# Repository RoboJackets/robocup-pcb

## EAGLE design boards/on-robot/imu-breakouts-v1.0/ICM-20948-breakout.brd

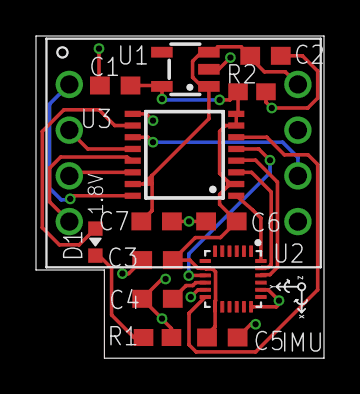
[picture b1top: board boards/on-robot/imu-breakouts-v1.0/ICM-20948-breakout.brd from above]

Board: 2 copper layers, 16.0 x 17.9 mm, 15 parts (1 on the bottom side), 16 nets.

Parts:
C1, C2: 1uF; C0603
C3, C4, C6, C7: 0.1uF; C0603
C5: 1.0uF; C0603
D1: GREEN; CHIP-LED0603
KIT1: IMU
R1: 220; R0603W
R2: 50k; R0603W
U1: NCP161; SOT-23-5
U2: ICM-20948
U3: TXB0106; TSSOP-16
U$1: ROBOBUZZ_0.4X

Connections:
!CS!/1.8V: U2.22, U3.4
!CS!/3.3V: KIT1.4, U3.13
+1.8V: C1.1, C3.1, C5.1, C6.1, R2.1, U1.5, U2.8, U2.13, U3.2, U3.7, U3.8
+1.8V-D1-OUT: D1.C, R1.2
+3.3V: C2.1, C7.1, KIT1.8, U1.1, U1.3, U3.15
CLK/1.8V: U2.23, U3.3
CLK/3.3V: KIT1.3, U3.14
GND: C1.2, C2.2, C3.2, C4.2, C5.2, C6.2, C7.2, KIT1.5, R1.1, R2.2, U1.2, U2.11, U2.18, U2.20, U3.9
INT/1.8V: U2.12, U3.6
INT/3.3V: KIT1.6, U3.11
MISO/1.8V: U2.9, U3.5
MISO/3.3V: KIT1.2, U3.12
MOSI/1.8V: U2.24, U3.1
MOSI/3.3V: KIT1.1, U3.16
PRE-LED-3.3V: D1.A, U3.10
REGOUT: C4.1, U2.10

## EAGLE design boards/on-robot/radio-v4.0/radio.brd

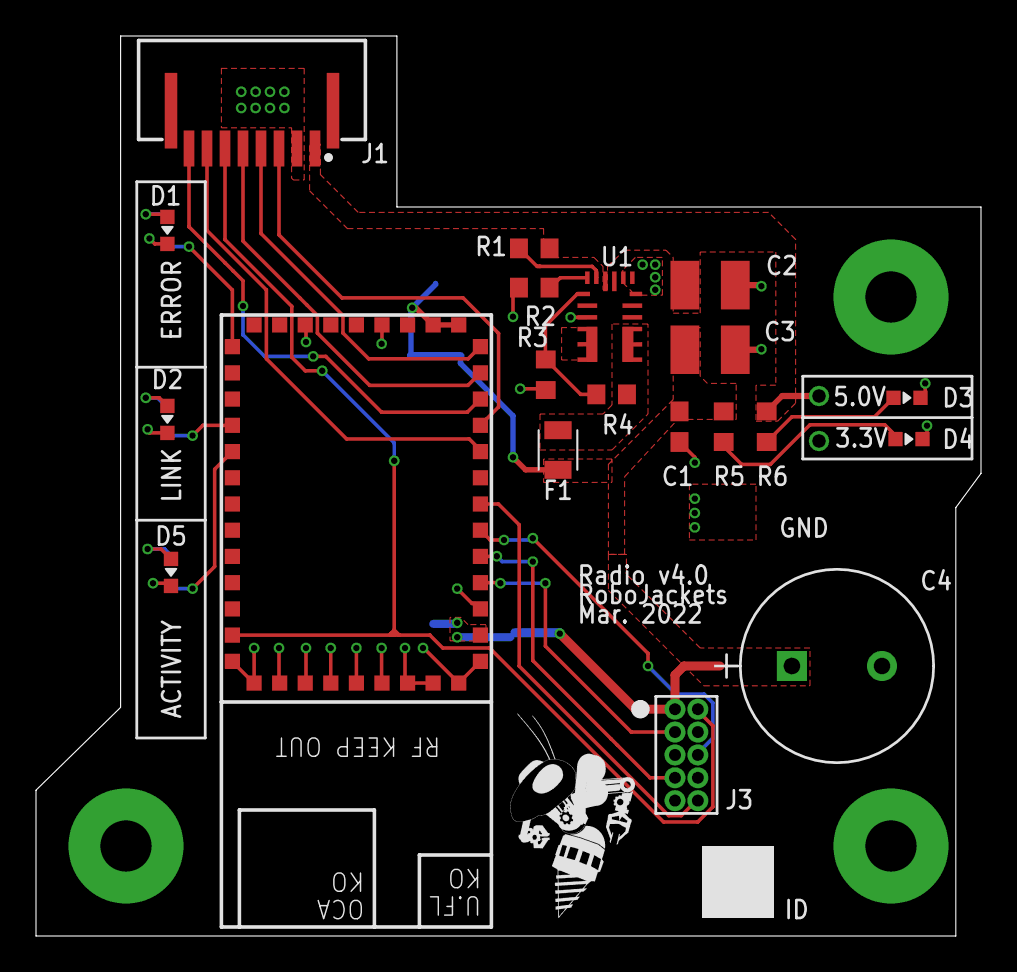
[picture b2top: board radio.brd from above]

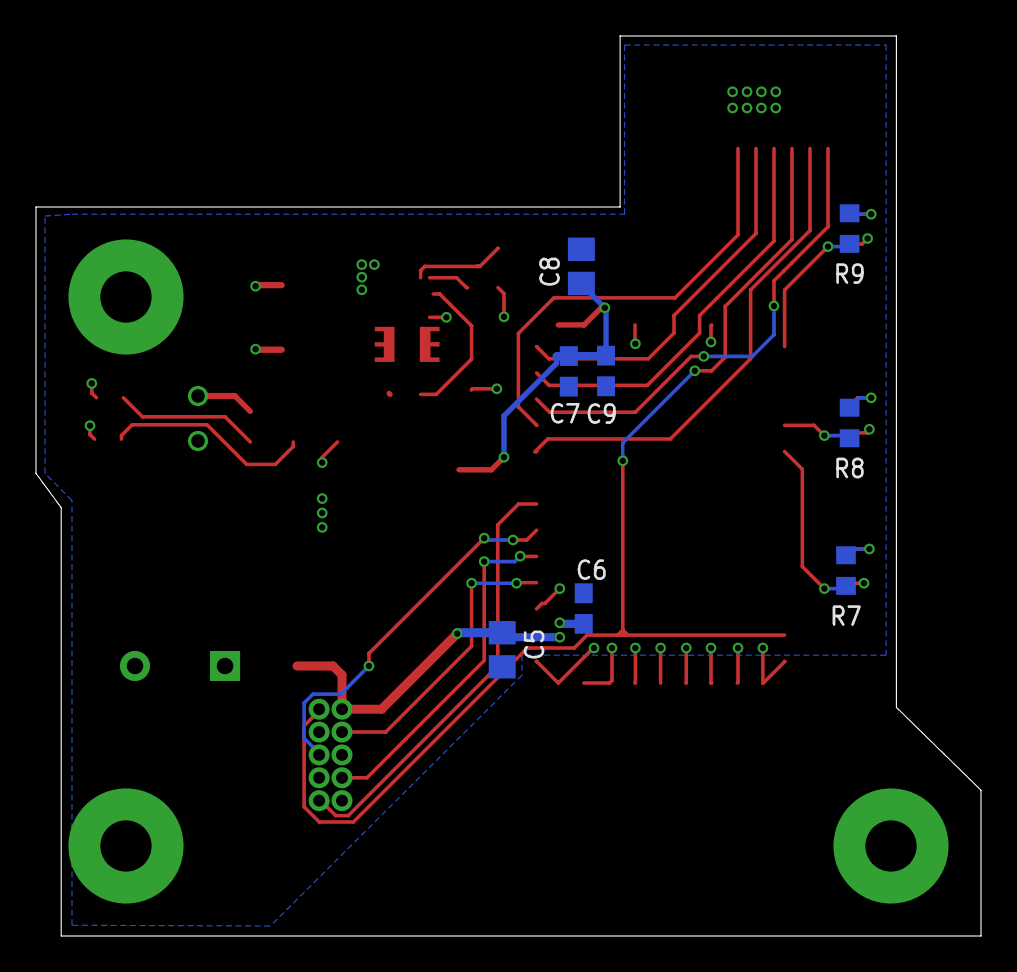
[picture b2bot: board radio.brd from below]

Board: 2 copper layers, 52.5 x 50.0 mm, 29 parts (8 on the bottom side), 25 nets.

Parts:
$$U1: ISM43340
C1, C6, C7: 0.1uF; C0603
C2: 10uF 16V; C1210
C3: 22uF; C1210
C4: 220uF; CAP_PAN_10X12.5
C5, C8: 10uF; C0805
C9: 1uF; C0603
D1: RED; CHIP-LED0603
D2, D3, D4: GREEN; CHIP-LED0603
D5: YELLOW; CHIP-LED0603
F1: 0805L200SLTHYR; FUSC2113X75
J1: SFW8; SFW8R-1ST
J2: FTSH-105-01-F-D-K; CONN_FTSH-105-01-F-D-K_SAI
R1: 100k; R0603
R2: 88.7k 1%; R0603
R3: 45.3k 1%; R0603
R4: 143.0k 1%; R0603
R5: 680; R0603
R6: 1k; R0603
R7, R8, R9: 200; R0603
U1: MPM3620GQV-P
U$2: ROBOBUZZ_0.6X

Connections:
3V3_PWR_IND: D4.A, R5.1
5V_PWR_IND: D3.A, R6.1
!CS!_RAD: $$U1.P$12, J1.5
!RST!_GLB: $$U1.P$34, J1.6, J2.2
+3.3V: $$U1.P$2, $$U1.P$14, $$U1.P$15, C1.1, C3.1, C4.1, C5.1, C6.1, C7.1, C8.1, C9.1, F1.2, J2.1, R5.2
+5.0V: C2.1, J1.1, R1.1, R6.2, U1.16
AAM: R2.2, U1.18
DBG_ACT_RAD: $$U1.P$27, R7.1
DBG_ERR: D1.A, R9.2
DBG_ERR_RAD: $$U1.P$23, R9.1
DBG_LNK_RAD: $$U1.P$26, R8.1
DGB_ACT: D5.A, R7.2
DGB_LNK: D2.A, R8.2
EN: R1.2, U1.17
FB: R3.2, R4.1, U1.1
GND: $$U1.P$1, $$U1.P$3, $$U1.P$17, $$U1.P$20, $$U1.P$35, $$U1.P$36, $$U1.P$37, $$U1.P$38, $$U1.P$39, $$U1.P$40, $$U1.P$41, $$U1.P$42, $$U1.P$43, $$U1.P$44, C1.2, C2.2, C3.2, C4.2, C5.2, C6.2, C7.2, C8.2, C9.2, D1.C, D2.C, D3.C, D4.C, D5.C, J1.2, J2.4, J2.5, J2.9, R2.1, R3.1, U1.3, U1.12, U1.13, U1.14
INT_RAD: $$U1.P$13, J1.4
MISO: $$U1.P$10, J1.3
MOSI: $$U1.P$9, J1.7
PRE-FUSE: F1.1, R4.2, U1.789
SCK: $$U1.P$11, J1.8
TCK_RAD: $$U1.P$5, J2.7
TDI_RAD: $$U1.P$6, J2.6
TDO_RAD: $$U1.P$7, J2.10
TMS_RAD: $$U1.P$4, J2.3

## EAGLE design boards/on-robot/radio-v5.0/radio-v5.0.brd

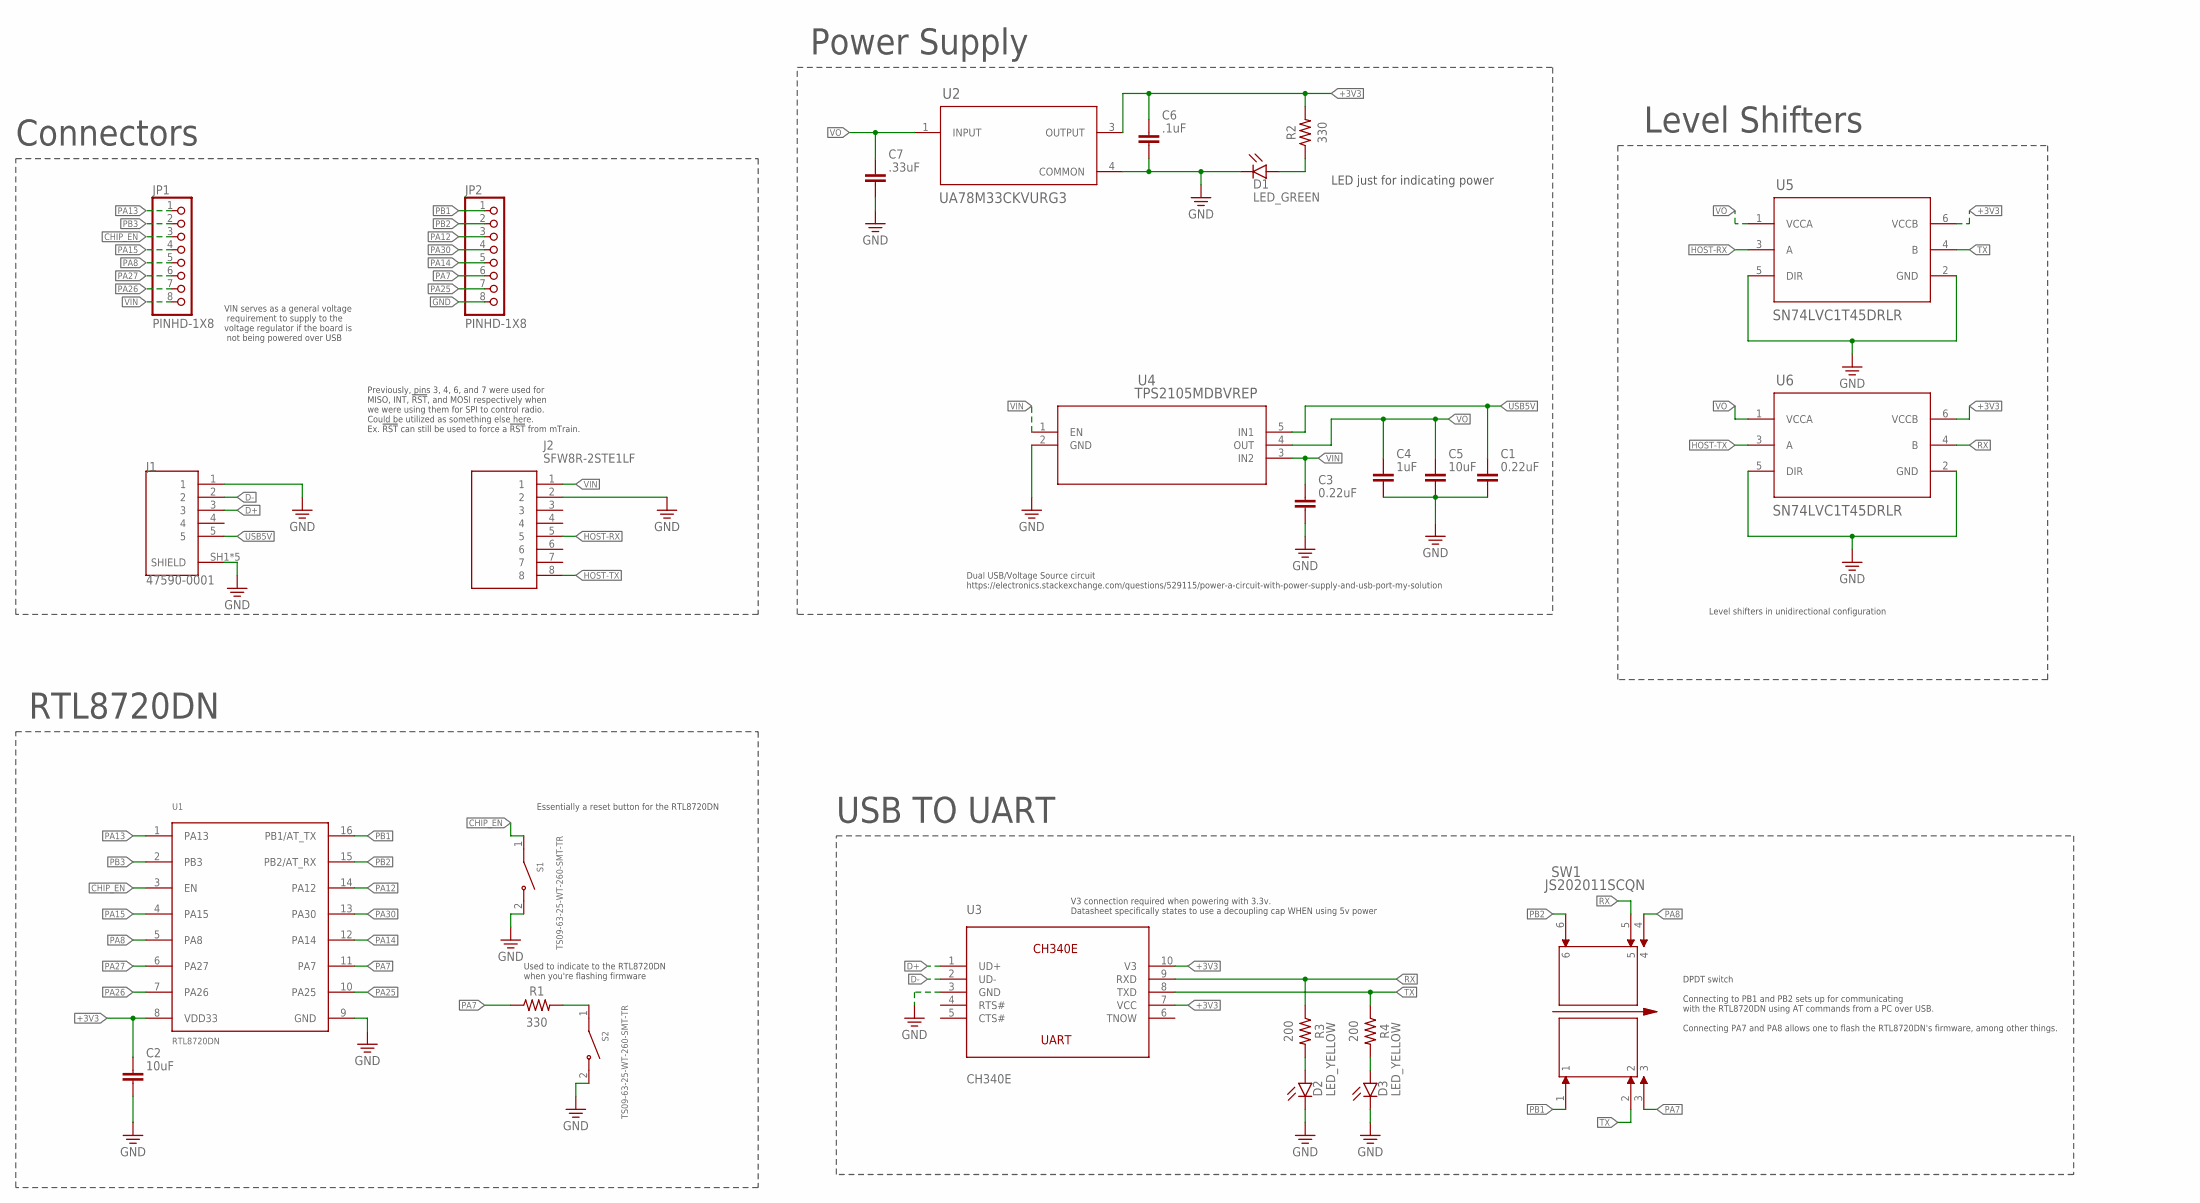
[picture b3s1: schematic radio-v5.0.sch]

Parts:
C1, C3: 0.22uF; CAPC1608X85
C2, C5: 10uF; CAPC1608X85
C4: 1uF; CAPC1608X85
C6: .1uF; CAPC1608X85
C7: .33uF; CAPC1608X85
D1: LED_GREEN; LEDC1608X55N_FLAT-B
D2, D3: LED_YELLOW; LEDC1608X55N_FLAT-B
J1: 47590-0001; MOLEX_47590-0001
J2: SFW8R-2STE1LF; SFW8R2STE1LF
JP1, JP2: PINHD-1X8; 1X08
R1, R2: 330; RESC1608X60
R3, R4: 200; RESC1608X60
S1, S2: TS09-63-25-WT-260-SMT-TR; SW_TS09-63-25-WT-260-SMT-TR
SW1: JS202011SCQN; SW_JS202011SCQN
U1: RTL8720DN
U2: UA78M33CKVURG3; KVU0003A_N
U3: CH340E; MS0P10
U4: TPS2105MDBVREP; DBV5_TEX
U5, U6: SN74LVC1T45DRLR; DRL0006A

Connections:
+3V3: C2.1, C6.1, R2.2, U1.8 (VDD33), U2.3 (OUTPUT), U3.7 (VCC), U3.10 (V3), U5.6 (VCCB), U6.6 (VCCB)
CHIP_EN: JP1.3, S1.1, U1.3 (EN)
D+: J1.3, U3.1 (UD+)
D-: J1.2, U3.2 (UD-)
GND: C1.2, C2.2, C3.2, C4.2, C5.2, C6.2, C7.2, D1.C, D2.C, D3.C, J1.SH1 (SHIELD), J1.SH2 (SHIELD), J1.SH3 (SHIELD), J1.SH4 (SHIELD), J1.SH5 (SHIELD), J2.2, JP2.8, S1.2, S2.2, U1.9 (GND), U2.4 (COMMON), U3.3 (GND), U4.2 (GND), U5.2 (GND), U5.5 (DIR), U6.2 (GND), U6.5 (DIR)
HOST-RX: J2.5, U5.3 (A)
HOST-TX: J2.8, U6.3 (A)
unnamed: R1.2, S2.1
unnamed: D2.A, R3.2
unnamed: D1.A, R2.1
unnamed: D3.A, R4.2
PA7: JP2.6, R1.1, SW1.3, U1.11 (PA7)
PA8: JP1.5, SW1.4, U1.5 (PA8)
PA12: JP2.3, U1.14 (PA12)
PA13: JP1.1, U1.1 (PA13)
PA14: JP2.5, U1.12 (PA14)
PA15: JP1.4, U1.4 (PA15)
PA25: JP2.7, U1.10 (PA25)
PA26: JP1.7, U1.7 (PA26)
PA27: JP1.6, U1.6 (PA27)
PA30: JP2.4, U1.13 (PA30)
PB1: JP2.1, SW1.1, U1.16 (PB1/AT_TX)
PB2: JP2.2, SW1.6, U1.15 (PB2/AT_RX)
PB3: JP1.2, U1.2 (PB3)
RX: R3.1, SW1.5, U3.9 (RXD), U6.4 (B)
TX: R4.1, SW1.2, U3.8 (TXD), U5.4 (B)
USB5V: C1.1, J1.5, U4.5 (IN1)
VIN: C3.1, J2.1, JP1.8, U4.1 (EN), U4.3 (IN2)
VO: C4.1, C5.1, C7.1, U2.1 (INPUT), U4.4 (OUT), U5.1 (VCCA), U6.1 (VCCA)

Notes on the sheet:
Connectors
VIN serves as a general voltage requirement to supply to the voltage regulator if the board is not being powered over USB
Power Supply
RTL8720DN
Dual USB/Voltage Source circuit https://electronics.stackexchange.com/questions/529115/power-a-circuit-with-power-supply-and-usb-port-my-solution
USB TO UART
DPDT switch Connecting to PB1 and PB2 sets up for communicating with the RTL8720DN using AT commands from a PC over USB. Connecting PA7 and PA8 allows one to flash the RTL8720DN's firmware, among other things.
V3 connection required when powering with 3.3v. Datasheet specifically states to use a decoupling cap WHEN using 5v power
Essentially a reset button for the RTL8720DN
Used to indicate to the RTL8720DN when you're flashing firmware
LED just for indicating power
Previously, pins 3, 4, 6, and 7 were used for MISO, INT, !RST!, and MOSI respectively when we were using them for SPI to control radio. Could be utilized as something else here. Ex. !RST! can still be used to force a !RST! from mTrain.
Level Shifters
Level shifters in unidirectional configuration

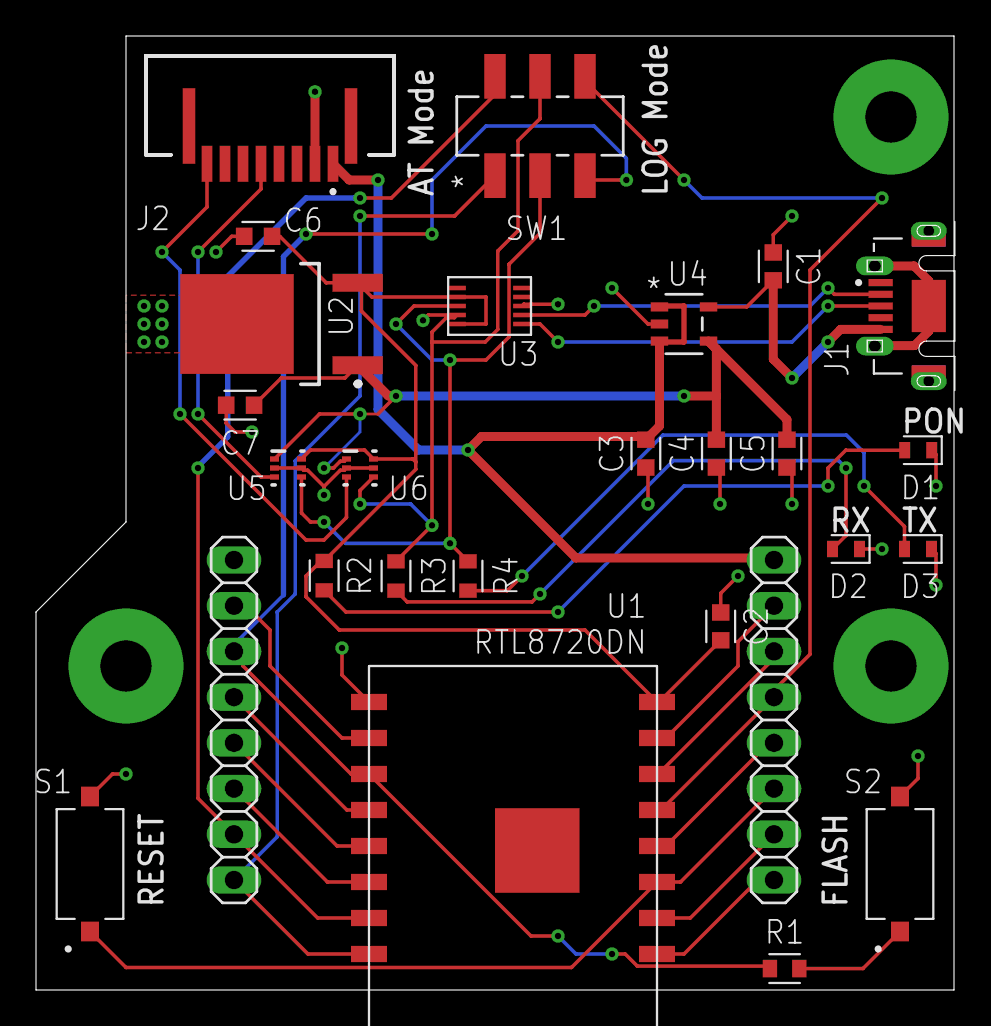
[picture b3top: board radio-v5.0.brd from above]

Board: 2 copper layers, 51.0 x 53.0 mm, 28 parts (1 on the bottom side), 29 nets.

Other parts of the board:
U$1: ROBOBUZZ_1.0X

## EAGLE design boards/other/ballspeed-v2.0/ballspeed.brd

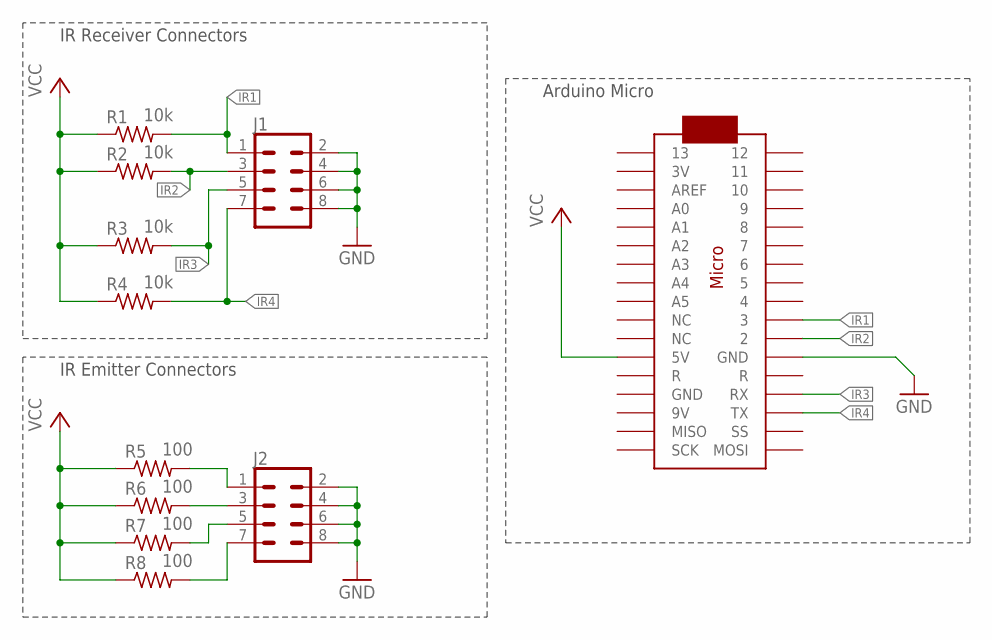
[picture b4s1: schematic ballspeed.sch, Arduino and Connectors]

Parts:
J1, J2: CONN_04X2; 2X4
R1, R2, R3, R4: 10k; R0603W
R5, R6, R7, R8: 100; R0603W
U$1: ARDUINOMICRO

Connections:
GND: J1.2, J1.4, J1.6, J1.8, J2.2, J2.4, J2.6, J2.8, U$1.P$21 (GND)
IR1: J1.1, R1.2 (PIN2), U$1.P$10 (3)
IR1-3.3V: J2.1, R5.2 (PIN2)
IR2: J1.3, R2.2 (PIN2), U$1.P$11 (2)
IR2-3.3V: J2.3, R6.2 (PIN2)
IR3: J1.5, R3.2 (PIN2), U$1.P$14 (RX)
IR3-3.3V: J2.5, R7.2 (PIN2)
IR4: J1.7, R4.2 (PIN2), U$1.P$15 (TX)
IR4-3.3V: J2.7, R8.2 (PIN2)
VCC: R1.1 (PIN1), R2.1 (PIN1), R3.1 (PIN1), R4.1 (PIN1), R5.1 (PIN1), R6.1 (PIN1), R7.1 (PIN1), R8.1 (PIN1), U$1.P$23 (5V)

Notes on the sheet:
IR Emitter Connectors
IR Receiver Connectors
Arduino Micro

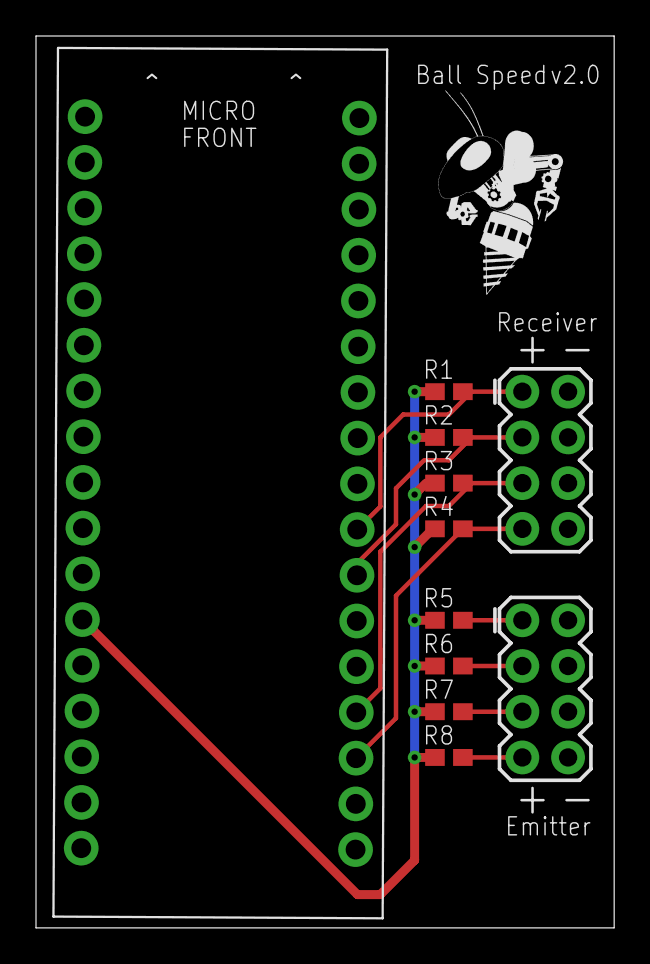
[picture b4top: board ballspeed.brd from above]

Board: 2 copper layers, 32.1 x 49.6 mm, 12 parts (0 on the bottom side), 10 nets.

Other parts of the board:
U$3: ROBOBUZZ_0.6X

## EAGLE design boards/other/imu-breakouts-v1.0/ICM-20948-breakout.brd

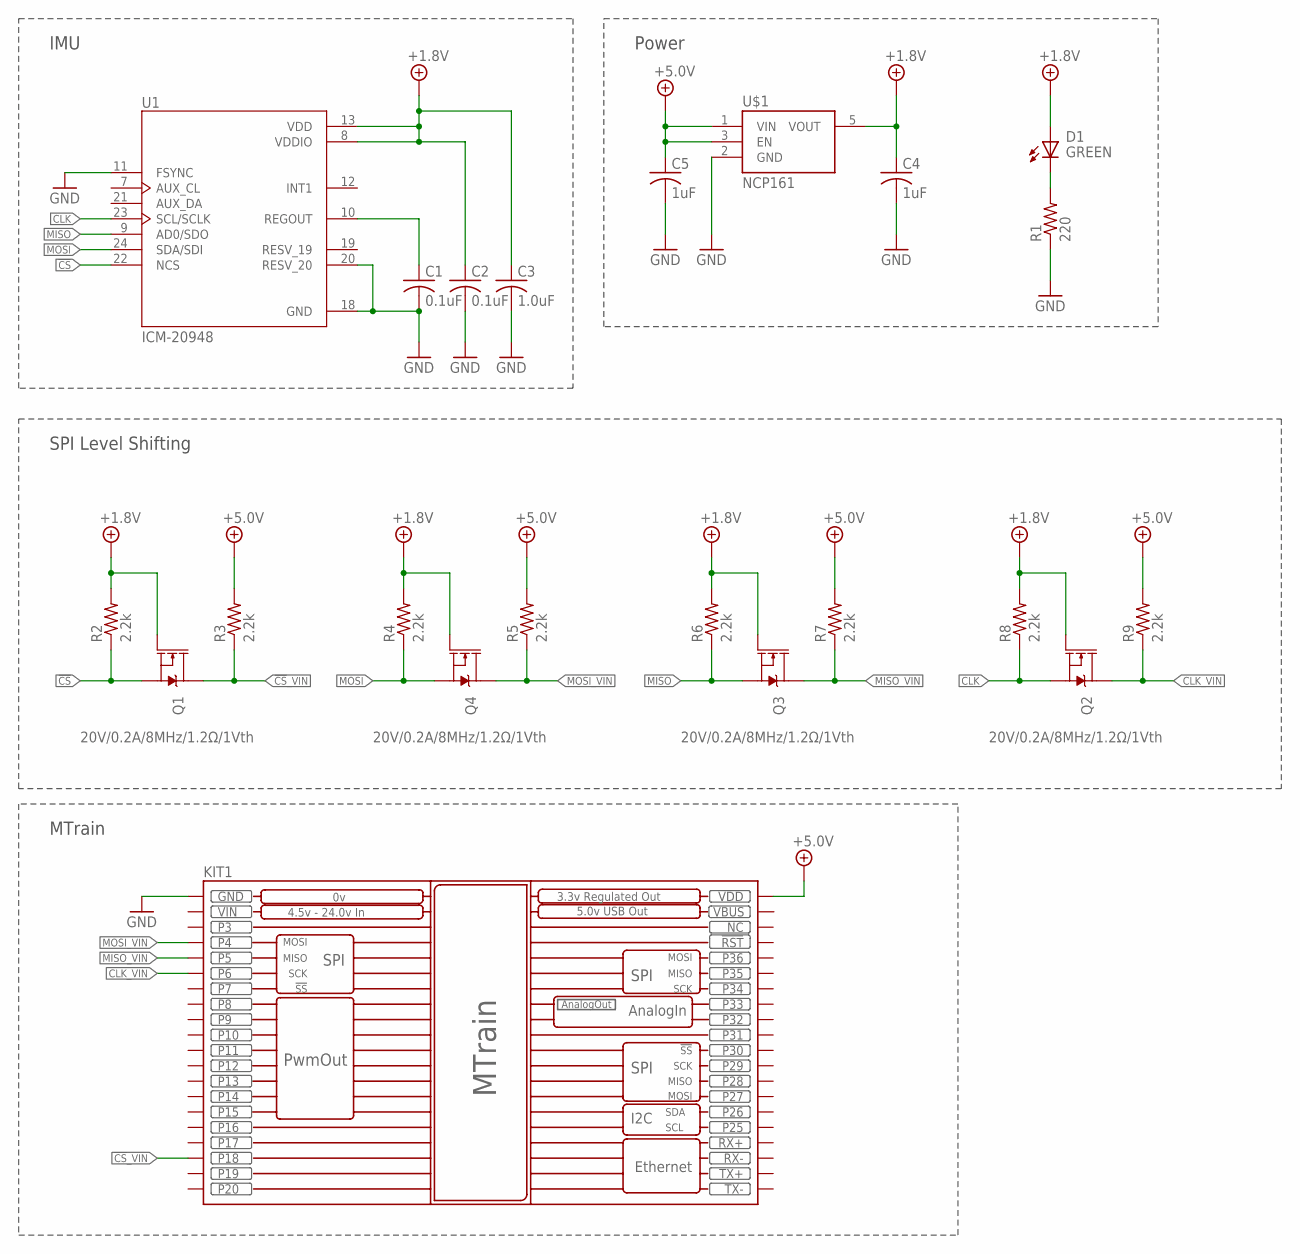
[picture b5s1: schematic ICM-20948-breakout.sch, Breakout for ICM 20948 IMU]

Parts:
C1, C2: 0.1uF; C0603
C3: 1.0uF; C0603
C4, C5: 1uF; C0603
D1: GREEN; CHIP-LED0603
KIT1: MTRAIN; MTRAIN-KIT
Q1, Q2, Q3, Q4: 20V/0.2A/8MHz/1.2Ω/1Vth; SOT-416FL
R1: 220; R0603W
R2, R3, R4, R5, R6, R7, R8, R9: 2.2k; R0603W
U1: ICM-20948
U$1: NCP161; SOT-23-5

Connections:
!CS!: Q1.2 (S), R2.1 (PIN1), U1.22 (NCS)
!CS!_VIN: KIT1.P$18 (P18), Q1.3 (D), R3.1 (PIN1)
+1.8V: C2.1, C3.1, C4.1, D1.A, Q1.1 (G), Q2.1 (G), Q3.1 (G), Q4.1 (G), R2.2 (PIN2), R4.2 (PIN2), R6.2 (PIN2), R8.2 (PIN2), U1.8 (VDDIO), U1.13 (VDD), U$1.5 (VOUT)
+3.3V: C5.1, R3.2 (PIN2), R5.2 (PIN2), R7.2 (PIN2), R9.2 (PIN2), U$1.1 (VIN), U$1.3 (EN)
+5.0V: KIT1.VDD
CLK: Q2.2 (S), R8.1 (PIN1), U1.23 (SCL/SCLK)
CLK_VIN: KIT1.P$6 (P6), Q2.3 (D), R9.1 (PIN1)
GND: C1.2, C2.2, C3.2, C4.2, C5.2, KIT1.GND, R1.1 (PIN1), U1.11 (FSYNC), U1.18 (GND), U1.20 (RESV_20), U$1.2 (GND)
MISO: Q3.2 (S), R6.1 (PIN1), U1.9 (AD0/SDO)
MISO_VIN: KIT1.P$5 (P5), Q3.3 (D), R7.1 (PIN1)
MOSI: Q4.2 (S), R4.1 (PIN1), U1.24 (SDA/SDI)
MOSI_VIN: KIT1.P$4 (P4), Q4.3 (D), R5.1 (PIN1)
unnamed: D1.C (K), R1.2 (PIN2)
REGOUT: C1.1, U1.10 (REGOUT)
VBUS: KIT1.VBUS
VIN: KIT1.VIN

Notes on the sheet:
IMU
MTrain
Power
SPI Level Shifting

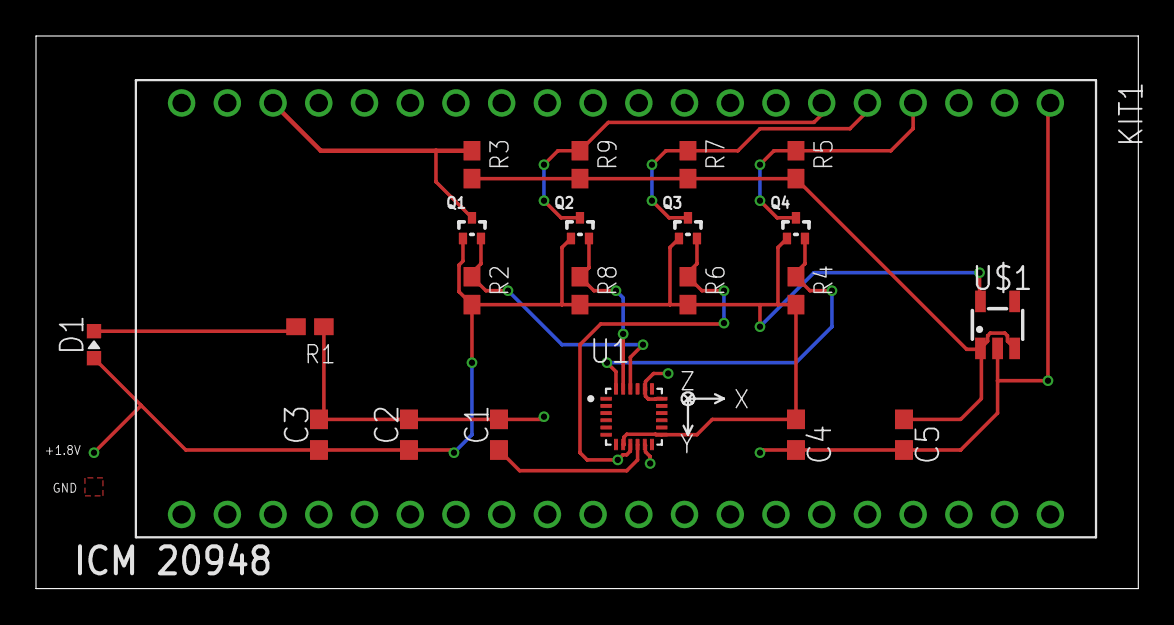
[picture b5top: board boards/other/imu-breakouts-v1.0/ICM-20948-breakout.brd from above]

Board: 2 copper layers, 61.2 x 30.7 mm, 22 parts (0 on the bottom side), 13 nets.

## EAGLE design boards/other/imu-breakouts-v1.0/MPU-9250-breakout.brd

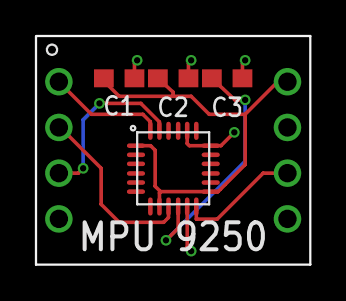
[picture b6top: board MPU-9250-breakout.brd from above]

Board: 2 copper layers, 15.2 x 12.7 mm, 5 parts (0 on the bottom side), 7 nets.

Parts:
C1: 0.01uF; C0603
C2, C3: 0.1uF; C0603
IC1: MPU-9250; QFN-24-4MM2
KIT1: IMUIMU-KIT; IMU-KIT

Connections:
+3.3V: C1.1, C2.1, IC1.1, IC1.8, IC1.13, KIT1.8
CLK: IC1.23, KIT1.3
GND: C1.2, C2.2, C3.2, IC1.11, IC1.18, IC1.20, KIT1.5
INT: IC1.12, KIT1.6
MISO: IC1.9, KIT1.2
MOSI: IC1.24, KIT1.1
unnamed: C3.1, IC1.10

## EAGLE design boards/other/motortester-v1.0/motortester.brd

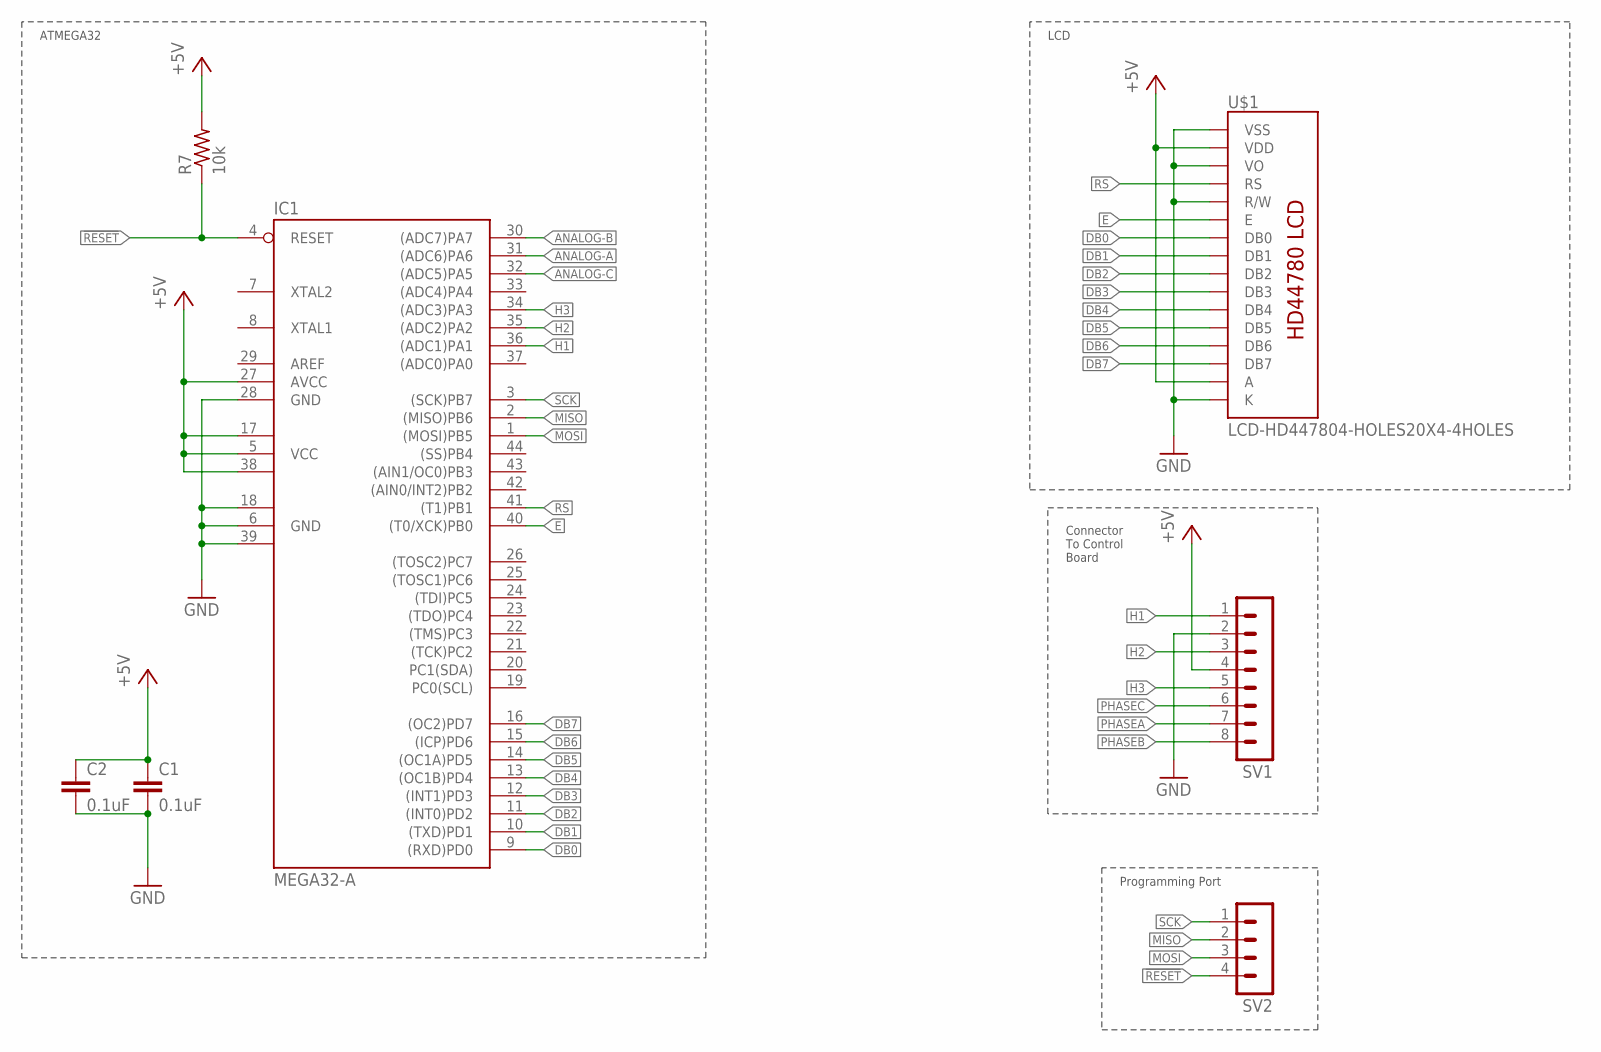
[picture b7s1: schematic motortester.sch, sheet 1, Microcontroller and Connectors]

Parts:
C1, C2: 0.1uF; C0603
IC1: MEGA32-A; TQFP44
R7: 10k; R0603
SV1: MA08-1
SV2: MA04-1
U$1: LCD-HD447804-HOLES20X4-4HOLES; LCD-20X4-4HOLES

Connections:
!RESET!: IC1.4 (RESET), R7.1, SV2.4
ANALOG-A: IC1.31 ((ADC6)PA6); also elsewhere on the board
ANALOG-B: IC1.30 ((ADC7)PA7); also elsewhere on the board
ANALOG-C: IC1.32 ((ADC5)PA5); also elsewhere on the board
DB0: IC1.9 ((RXD)PD0), U$1.P$7 (DB0)
DB1: IC1.10 ((TXD)PD1), U$1.P$8 (DB1)
DB2: IC1.11 ((INT0)PD2), U$1.P$9 (DB2)
DB3: IC1.12 ((INT1)PD3), U$1.P$10 (DB3)
DB4: IC1.13 ((OC1B)PD4), U$1.P$11 (DB4)
DB5: IC1.14 ((OC1A)PD5), U$1.P$12 (DB5)
DB6: IC1.15 ((ICP)PD6), U$1.P$13 (DB6)
DB7: IC1.16 ((OC2)PD7), U$1.P$14 (DB7)
E: IC1.40 ((T0/XCK)PB0), U$1.P$6 (E)
GND: C1.2, C2.2, IC1.6 (GND), IC1.18 (GND1), IC1.28 (GND), IC1.39 (GND2), SV1.2, U$1.P$1 (VSS), U$1.P$3 (VO), U$1.P$5 (R/W), U$1.P$16 (K)
H1: IC1.36 ((ADC1)PA1), SV1.1
H2: IC1.35 ((ADC2)PA2), SV1.3
H3: IC1.34 ((ADC3)PA3), SV1.5
MISO: IC1.2 ((MISO)PB6), SV2.2
MOSI: IC1.1 ((MOSI)PB5), SV2.3
PHASEA: SV1.7; also elsewhere on the board
PHASEB: SV1.8; also elsewhere on the board
PHASEC: SV1.6; also elsewhere on the board
RS: IC1.41 ((T1)PB1), U$1.P$4 (RS)
SCK: IC1.3 ((SCK)PB7), SV2.1
VCC: C1.1, C2.1, IC1.5 (VCC), IC1.17 (VCC1), IC1.27 (AVCC), IC1.38 (VCC2), R7.2, SV1.4, U$1.P$2 (VDD), U$1.P$15 (A)

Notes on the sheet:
ATMEGA32
LCD
Connector To Control Board
Programming Port

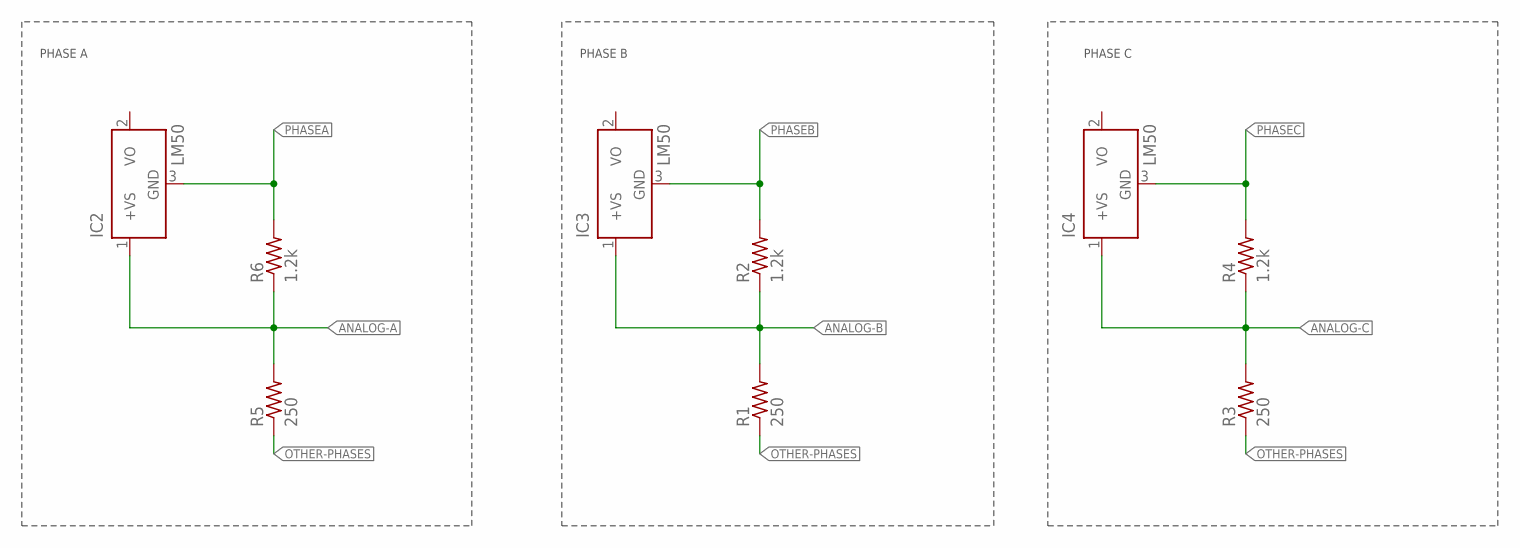
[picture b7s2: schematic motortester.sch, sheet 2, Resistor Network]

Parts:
IC2, IC3, IC4: LM50; SOT23
R1, R3, R5: 250; R0603
R2, R4, R6: 1.2k; R0603

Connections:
ANALOG-A: IC2.1 (+VS), R5.2, R6.1; also elsewhere on the board
ANALOG-B: IC3.1 (+VS), R1.2, R2.1; also elsewhere on the board
ANALOG-C: IC4.1 (+VS), R3.2, R4.1; also elsewhere on the board
OTHER-PHASES: R1.1, R3.1, R5.1
PHASEA: IC2.3 (GND), R6.2; also elsewhere on the board
PHASEB: IC3.3 (GND), R2.2; also elsewhere on the board
PHASEC: IC4.3 (GND), R4.2; also elsewhere on the board

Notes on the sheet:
PHASE A
PHASE B
PHASE C

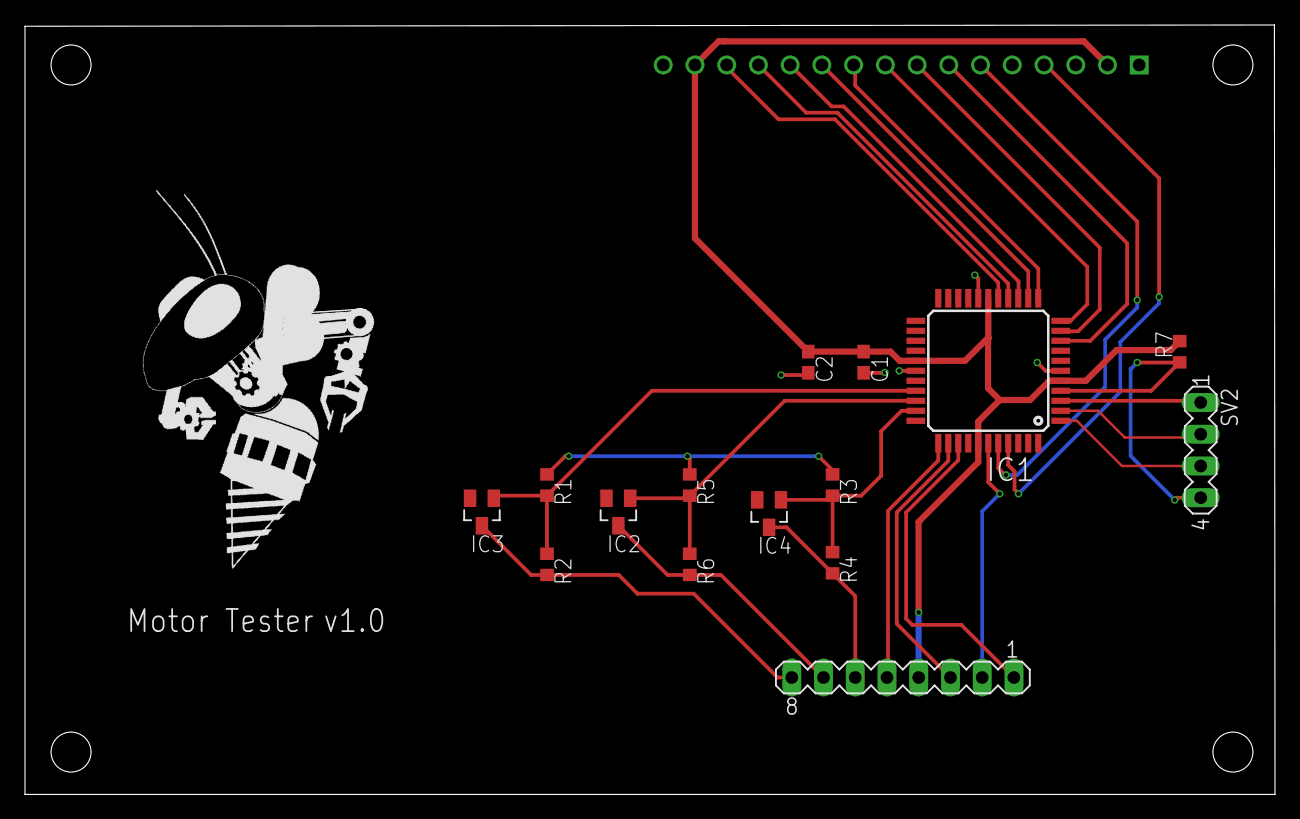
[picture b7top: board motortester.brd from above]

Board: 2 copper layers, 100.1 x 61.6 mm, 17 parts (1 on the bottom side), 26 nets.

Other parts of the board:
U$2: ROBOBUZZ_1.4X

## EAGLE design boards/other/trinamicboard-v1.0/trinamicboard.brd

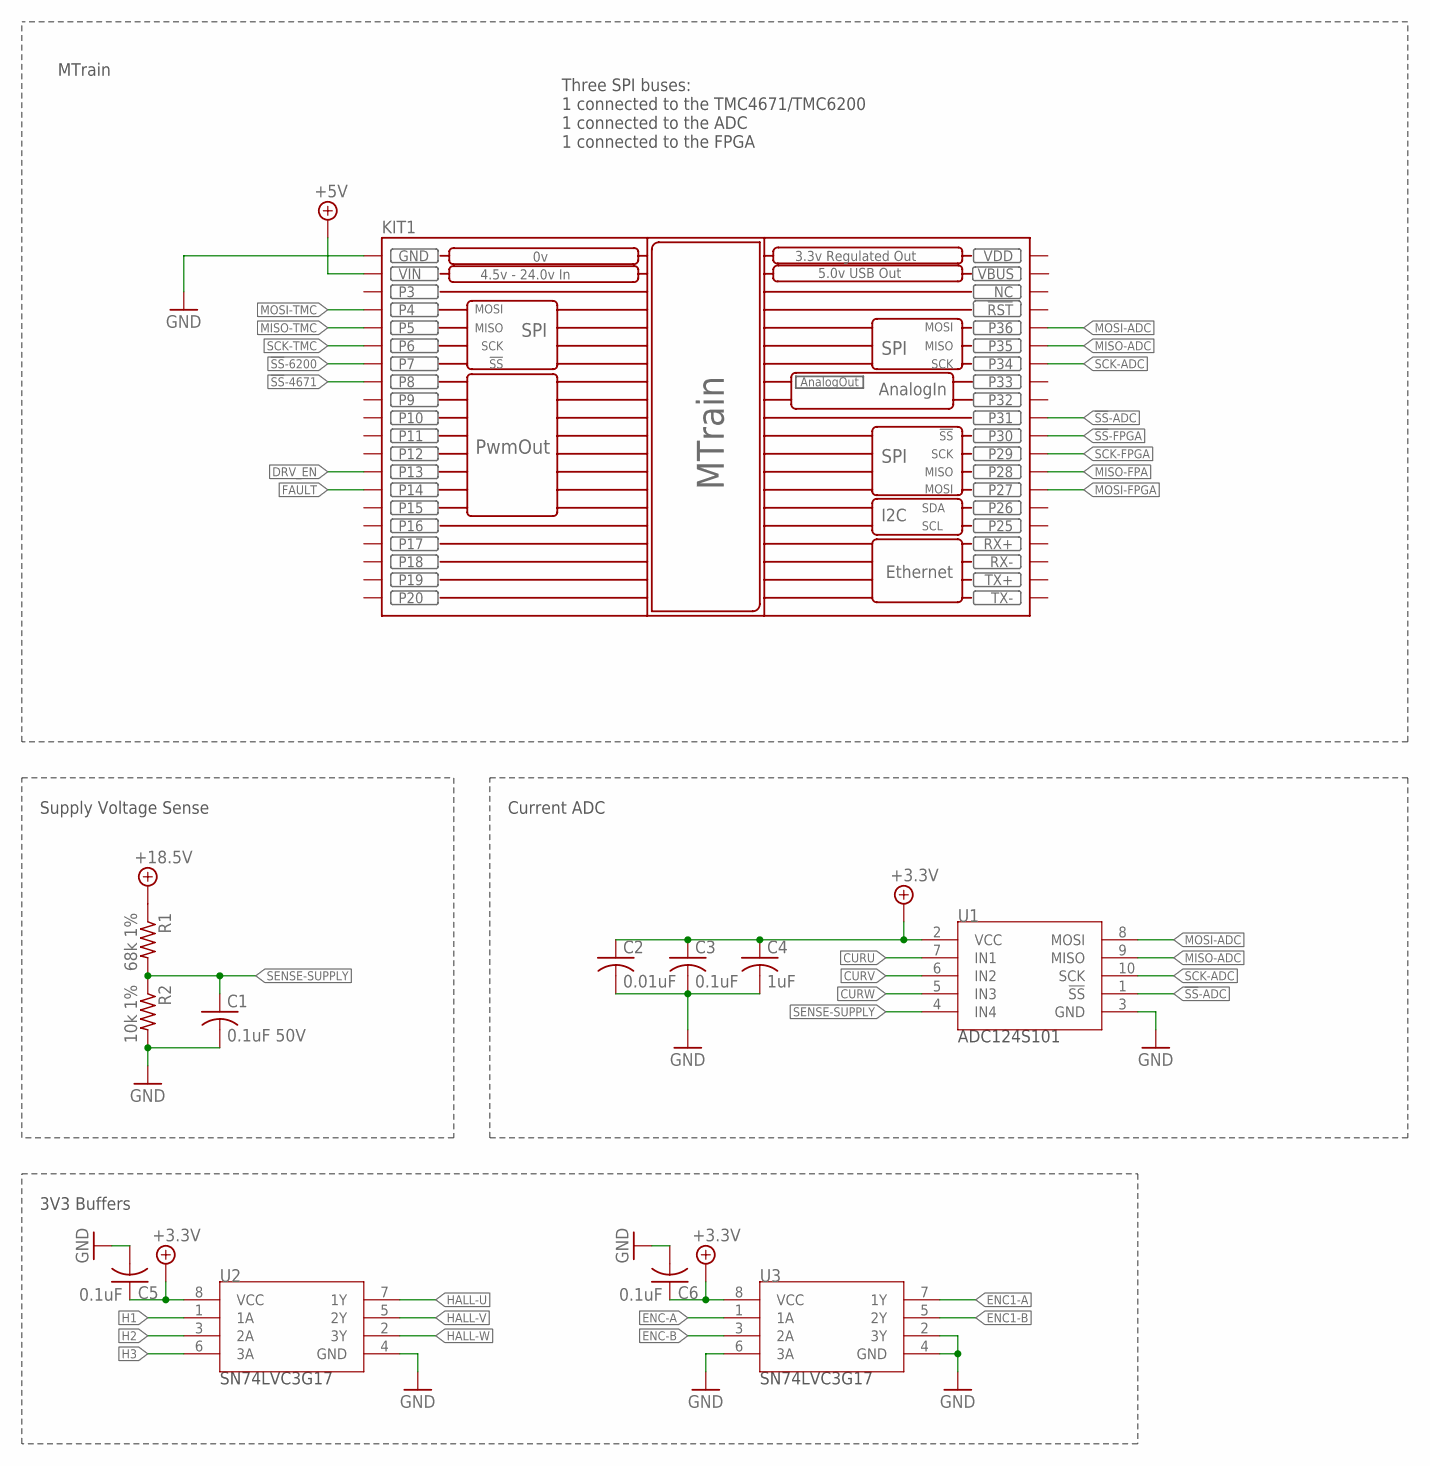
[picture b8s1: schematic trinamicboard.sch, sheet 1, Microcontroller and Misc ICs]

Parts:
C1: 0.1uF 50V; C0603
C2: 0.01uF; C0603
C3, C5, C6: 0.1uF; C0603
C4: 1uF; C0603
KIT1: MTRAIN; MTRAIN-KIT
R1: 68k 1%; R0603
R2: 10k 1%; R0603
U1: ADC124S101; VSSOP-10
U2, U3: SN74LVC3G17; VSSOP-8

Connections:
2+5V: KIT1.VIN; also elsewhere on the board
!SS!-4671: KIT1.P$8 (P8); also elsewhere on the board
!SS!-6200: KIT1.P$7 (P7); also elsewhere on the board
!SS!-ADC: KIT1.P$31 (P31), U1.1 (!SS); also elsewhere on the board
!SS!-FPGA: KIT1.P$30 (P30); also elsewhere on the board
+3.3V: C2.1, C3.1, C4.1, C5.1, C6.1, U1.2 (VCC), U2.8 (VCC), U3.8 (VCC); also elsewhere on the board
+18.5V: R1.1; also elsewhere on the board
CURU: U1.7 (IN1); also elsewhere on the board
CURV: U1.6 (IN2); also elsewhere on the board
CURW: U1.5 (IN3); also elsewhere on the board
DRV_EN: KIT1.P$13 (P13); also elsewhere on the board
ENC1-A: U3.7 (1Y); also elsewhere on the board
ENC1-B: U3.5 (2Y); also elsewhere on the board
ENC-A: U3.1 (1A); also elsewhere on the board
ENC-B: U3.3 (2A); also elsewhere on the board
FAULT: KIT1.P$14 (P14); also elsewhere on the board
GND: C1.2, C2.2, C3.2, C4.2, C5.2, C6.2, KIT1.GND, R2.2, U1.3 (GND), U2.4 (GND), U3.2 (3Y), U3.4 (GND), U3.6 (3A); also elsewhere on the board
H1: U2.1 (1A); also elsewhere on the board
H2: U2.3 (2A); also elsewhere on the board
H3: U2.6 (3A); also elsewhere on the board
HALL-U: U2.7 (1Y); also elsewhere on the board
HALL-V: U2.5 (2Y); also elsewhere on the board
HALL-W: U2.2 (3Y); also elsewhere on the board
MISO-ADC: KIT1.P$35 (P35), U1.9 (MISO); also elsewhere on the board
MISO-FPA: KIT1.P$28 (P28)
MISO-TMC: KIT1.P$5 (P5); also elsewhere on the board
MOSI-ADC: KIT1.P$36 (P36), U1.8 (MOSI); also elsewhere on the board
MOSI-FPGA: KIT1.P$27 (P27); also elsewhere on the board
MOSI-TMC: KIT1.P$4 (P4); also elsewhere on the board
SCK-ADC: KIT1.P$34 (P34), U1.10 (SCK); also elsewhere on the board
SCK-FPGA: KIT1.P$29 (P29); also elsewhere on the board
SCK-TMC: KIT1.P$6 (P6); also elsewhere on the board
SENSE-SUPPLY: C1.1, R1.2, R2.1, U1.4 (IN4)
VBUS: KIT1.VBUS
VDD: KIT1.VDD

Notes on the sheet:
MTrain
Supply Voltage Sense
Three SPI buses: 1 connected to the TMC4671/TMC6200 1 connected to the ADC 1 connected to the FPGA
Current ADC
3V3 Buffers

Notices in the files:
parts and their libraries:
COPYRIGHT: Copyright (C) 2022 Ultra Librarian. All rights reserved.
SparkFun-Connectors: Licensing: Creative Commons ShareAlike 4.0 International - https://creativecommons.org/licenses/by-sa/4.0
